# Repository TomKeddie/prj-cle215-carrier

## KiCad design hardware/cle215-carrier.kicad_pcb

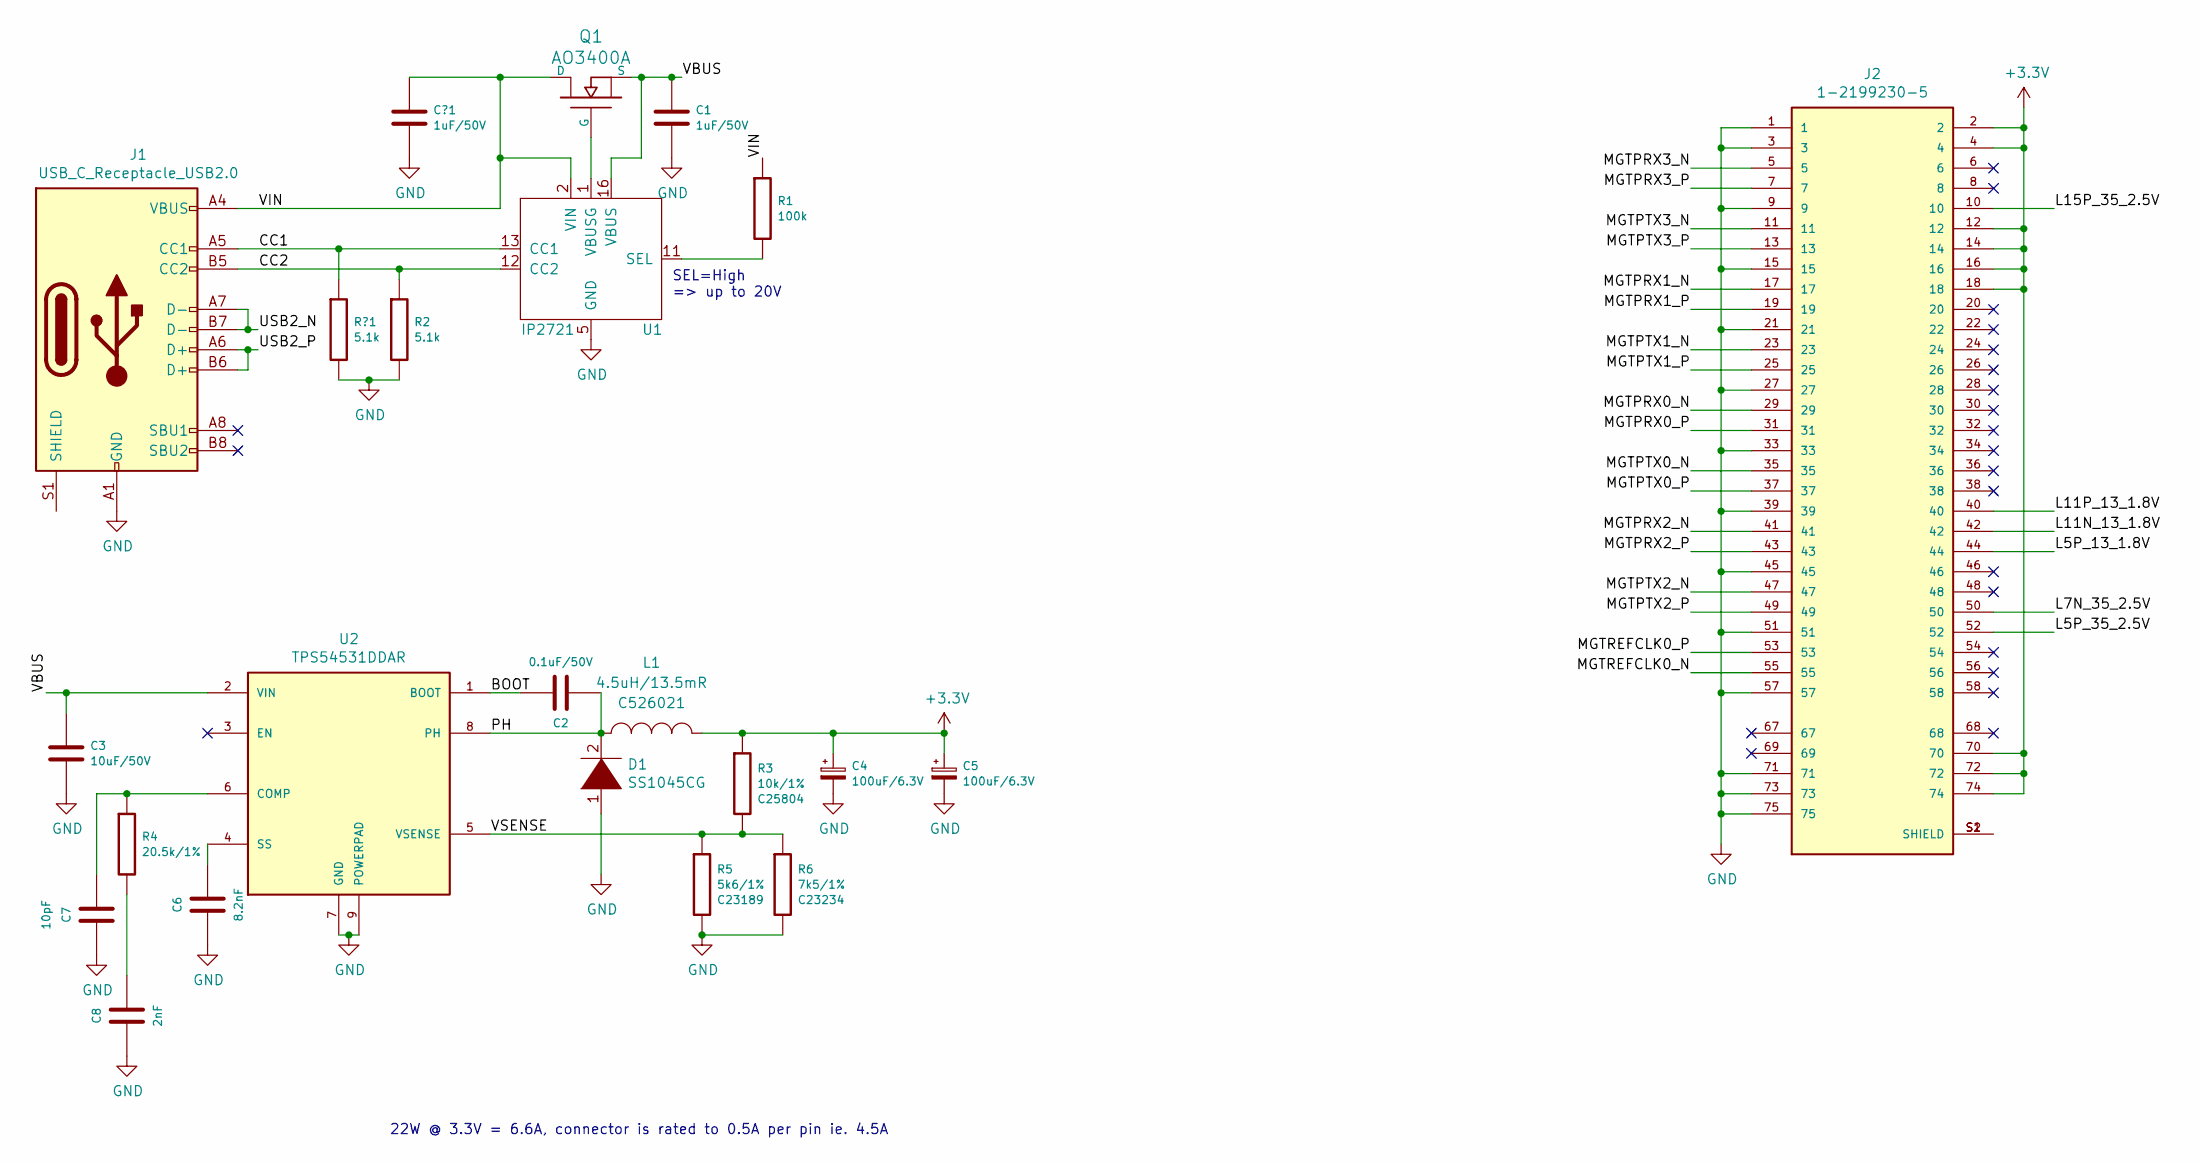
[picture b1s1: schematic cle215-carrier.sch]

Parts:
C1: 1uF/50V; C_0603_1608Metric
C2: 0.1uF/50V; C_0603_1608Metric
C3: 10uF/50V; C_0603_1608Metric
C4, C5: 100uF/6.3V; CP_EIA-3528-15_AVX-H
C6: 8.2nF; C_0603_1608Metric
C7: 10pF; C_0603_1608Metric
C8: 2nF; C_0603_1608Metric
C?1: 1uF/50V; C_0603_1608Metric
D1: SS1045CG; D_SMC; LCSC C475755
J1: USB_C_Receptacle_USB2.0; USB_C_Receptacle_GT-USB-7010
J2: 1-2199230-5; TE_1-2199230-5
L1: 4.5uH/13.5mR; L_FXL1360; LCSC C526021
Q1: AO3400A; SOT-23-FET-GSD
R1: 100k; R_0603_1608Metric
R2: 5.1k; R_0603_1608Metric
R3: 10k/1%; R_0603_1608Metric; LCSC C25804
R4: 20.5k/1%; R_0603_1608Metric
R5: 5k6/1%; R_0603_1608Metric; LCSC C23189
R6: 7k5/1%; R_0603_1608Metric; LCSC C23234
R?1: 5.1k; R_0603_1608Metric
U1: IP2721; SSOP-16_4.4x5.2mm_P0.65mm
U2: TPS54531DDAR; CONV_TPS54531DDAR; PARTREV A; LCSC C50605

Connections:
+3V3: C4.1, C5.1, J2.2, J2.4, J2.12, J2.14, J2.16, J2.18, J2.70, J2.72, J2.74, L1.2, R3.1
/BOOT: C2.2, U2.1 (BOOT)
/CC1: J1.A5 (CC1), R?1.1, U1.13 (CC1)
/CC2: J1.B5 (CC2), R2.1, U1.12 (CC2)
/L5P_13_1.8V: J2.44
/L5P_35_2.5V: J2.52
/L7N_35_2.5V: J2.50
/L11N_13_1.8V: J2.42
/L11P_13_1.8V: J2.40
/L15P_35_2.5V: J2.10
/PH: C2.1, D1.2 (A), L1.1, U2.8 (PH)
/USB2_N: J1.A7 (D-), J1.B7 (D-)
/USB2_P: J1.A6 (D+), J1.B6 (D+)
/VBUS: C1.1, C3.1, Q1.S, U1.16 (VBUS), U2.2 (VIN)
/VIN: C?1.1, J1.A4 (VBUS), J1.A9 (VBUS), J1.B4 (VBUS), J1.B9 (VBUS), Q1.D, R1.1, U1.2 (VIN)
/VSENSE: R3.2, R5.1, R6.1, U2.5 (VSENSE)
GND: C1.2, C3.2, C4.2, C5.2, C6.1, C7.1, C8.1, C?1.2, D1.1 (K), J1.A1 (GND), J1.A12 (GND), J1.B1 (GND), J1.B12 (GND), J2.1, J2.3, J2.9, J2.15, J2.21, J2.27, J2.33, J2.39, J2.45, J2.51, J2.57, J2.71, J2.73, J2.75, R2.2, R5.2, R6.2, R?1.2, U1.5 (GND), U2.7 (GND), U2.9 (POWERPAD)
unnamed: C6.2, U2.4 (SS)
unnamed: C7.2, R4.1, U2.6 (COMP)
unnamed: C8.2, R4.2
unnamed: J2.S1 (SHIELD), J2.S2 (SHIELD)
unnamed: Q1.G, U1.1 (VBUSG)
unnamed: R1.2, U1.11 (SEL)

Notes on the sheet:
SEL=High => up to 20V
22W @ 3.3V = 6.6A, connector is rated to 0.5A per pin ie. 4.5A

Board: 2 copper layers, 23 parts (21 on the bottom side), 17 nets, no tracks yet.

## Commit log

2021-01-14 hardware: first pass at power supply
